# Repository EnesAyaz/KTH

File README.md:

# KTH
This repository is opened to be archival information for my coming Ph.D studies at KTH.

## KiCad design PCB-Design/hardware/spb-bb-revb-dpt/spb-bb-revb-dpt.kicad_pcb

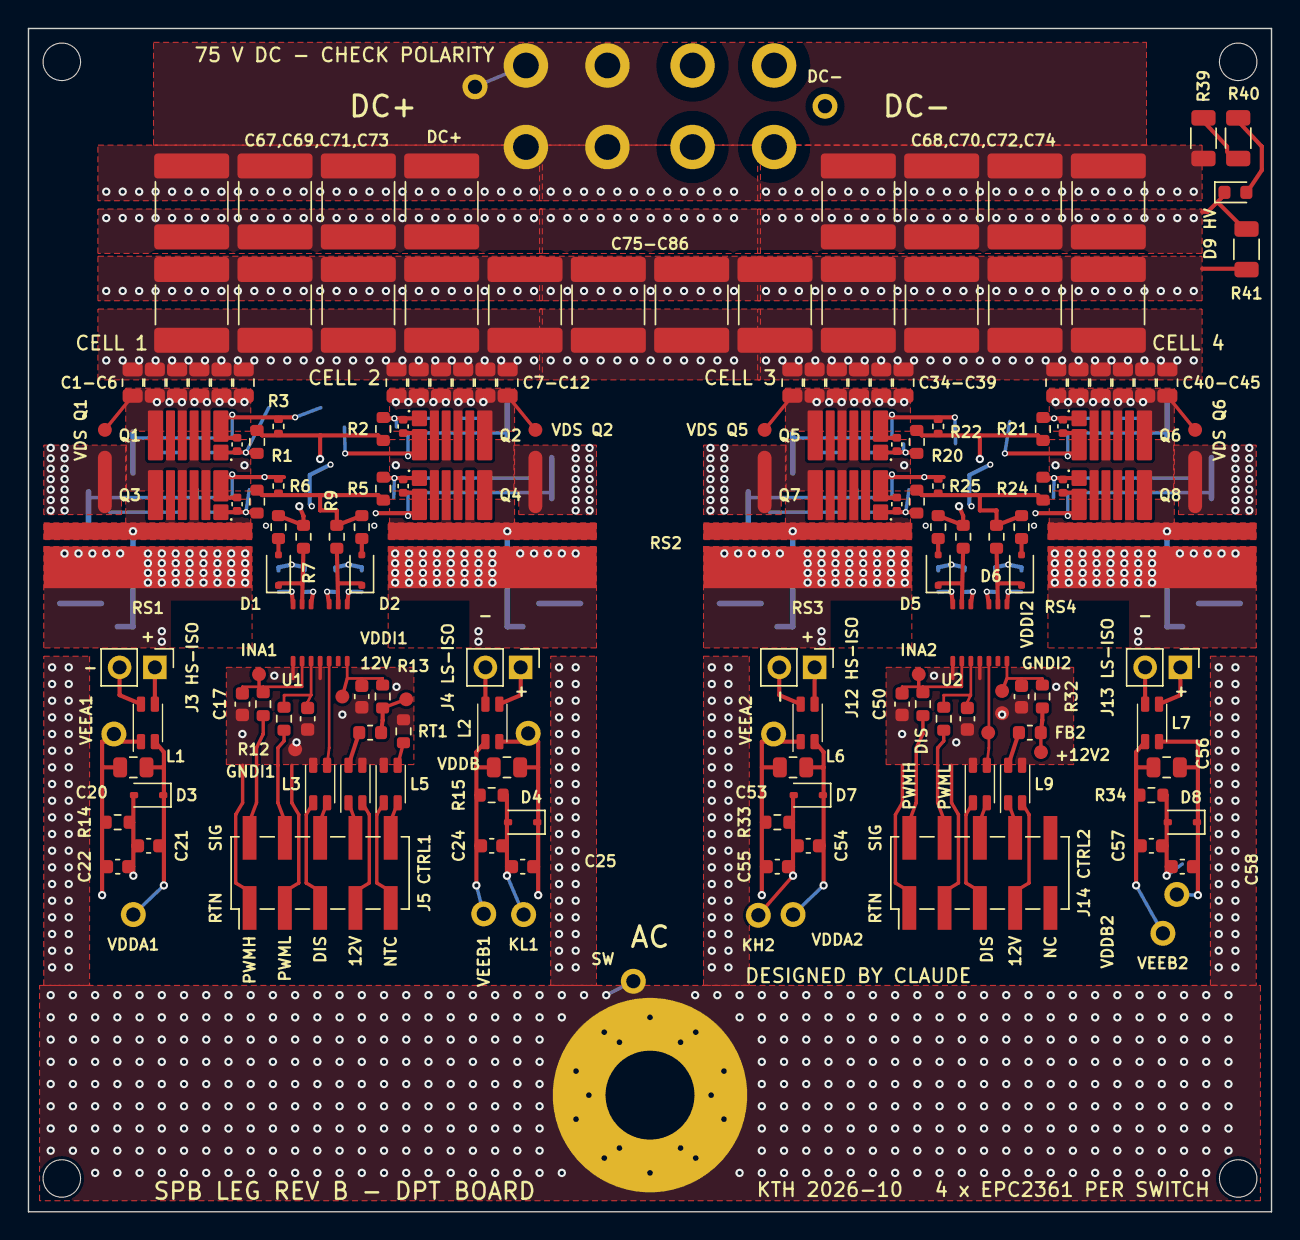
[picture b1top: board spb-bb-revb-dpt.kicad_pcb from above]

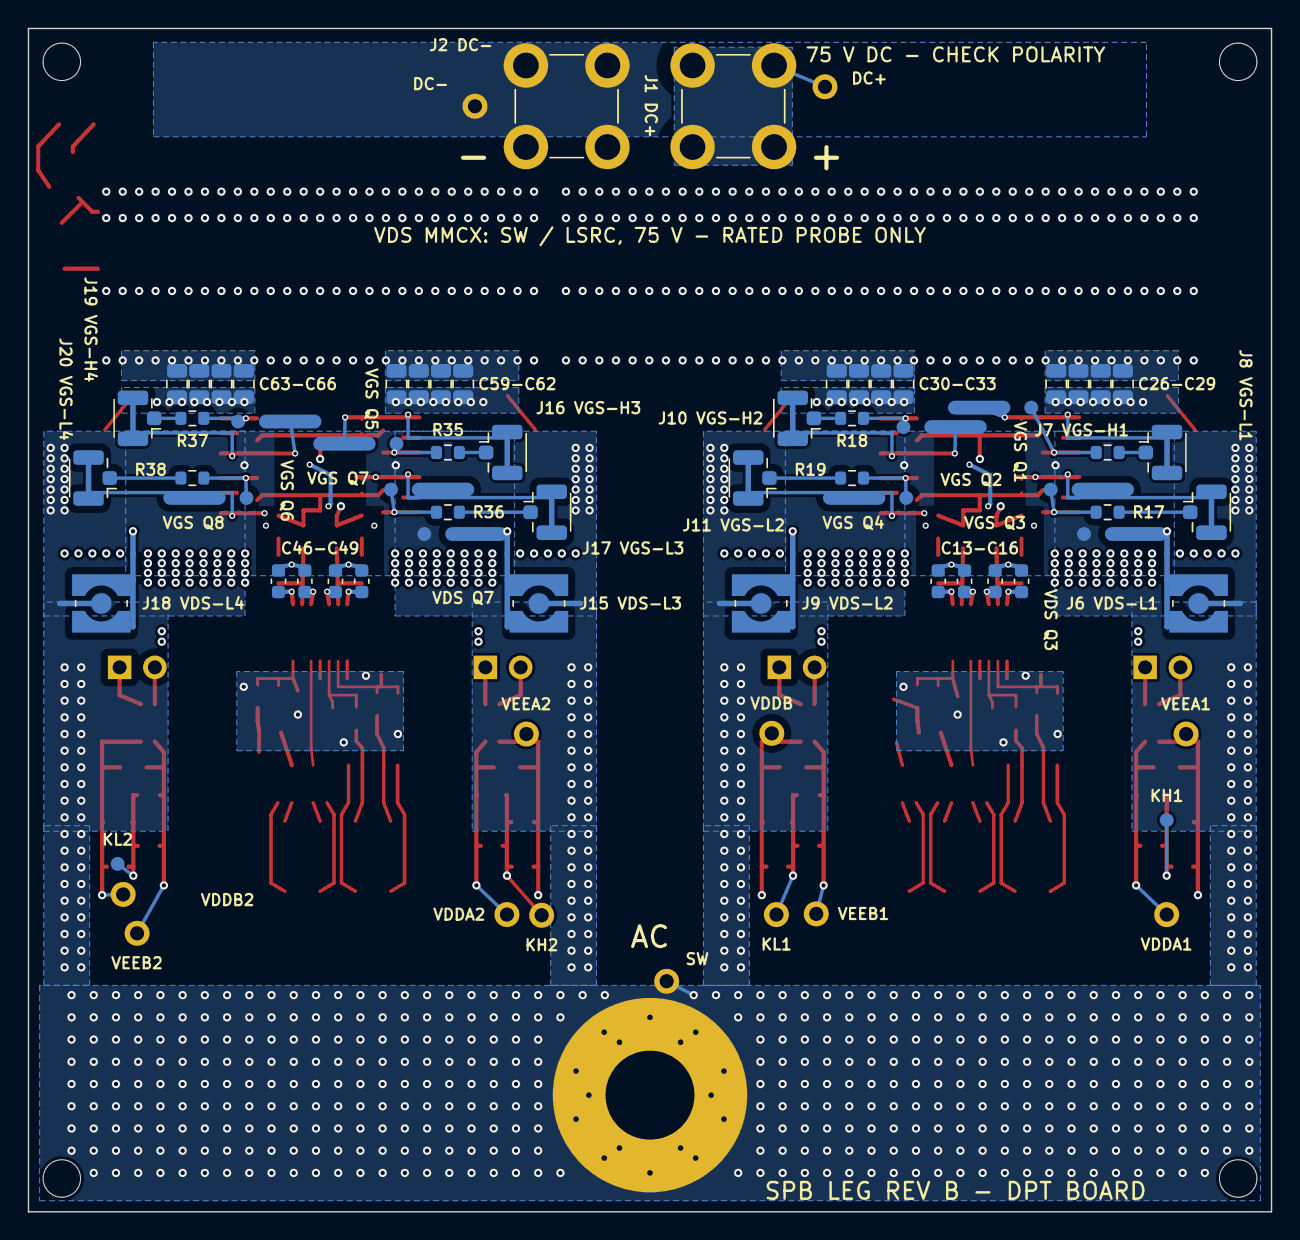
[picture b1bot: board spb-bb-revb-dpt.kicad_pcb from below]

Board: 4 copper layers, 89.5 x 85.2 mm, 233 parts (67 on the bottom side), 86 nets.

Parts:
C1, C2, C3, C4, C5, C6, C7, C8, C9, C10, C11, C12, C26, C27, C28, C29, C30, C31, C32, C33, C34, C35, C36, C37, C38, C39, C40, C41, C42, C43, C44, C45, C59, C60, C61, C62, C63, C64, C65, C66: 1uF 100V X7S; C_0805_2012Metric_TightCrtYd
C13, C14, C15, C16, C46, C47, C48, C49: 1uF 25V X7R 0603; C_0603_1608Metric
C17, C18, C50, C51: 100pF C0G 0603; C_0603_1608Metric
C19, C52: 22nF 25V X7R 0603; C_0603_1608Metric
C20, C23, C53, C56: 4.7uF 25V X7R 0805; C_0805_2012Metric
C21, C22, C24, C25, C54, C55, C57, C58: 4.7uF 16V X5R 0603; C_0603_1608Metric
C67, C68, C69, C70, C71, C72, C73, C74, C75, C76, C77, C78, C79, C80, C81, C82, C83, C84, C85, C86: 22uF 100V X7S 2220; C_2220_5750Metric_TightCrtYd
C87: DNP C_GS (Q1 gate-Kelvin, fit for tests); C_0402_1005Metric_TightCrtYd
C88: DNP C_GS (Q2 gate-Kelvin, fit for tests); C_0402_1005Metric_TightCrtYd
C89: DNP C_GS (Q3 gate-Kelvin, fit for tests); C_0402_1005Metric_TightCrtYd
C90: DNP C_GS (Q4 gate-Kelvin, fit for tests); C_0402_1005Metric_TightCrtYd
C91: DNP C_GS (Q5 gate-Kelvin, fit for tests); C_0402_1005Metric_TightCrtYd
C92: DNP C_GS (Q6 gate-Kelvin, fit for tests); C_0402_1005Metric_TightCrtYd
C93: DNP C_GS (Q7 gate-Kelvin, fit for tests); C_0402_1005Metric_TightCrtYd
C94: DNP C_GS (Q8 gate-Kelvin, fit for tests); C_0402_1005Metric_TightCrtYd
D1, D2, D5, D6: PMEG3020EJ; D_SOD-323F
D3, D4, D7, D8: BZX384-C5V1; D_SOD-323
D9: red 0603 (DC link present); LED_0603_1608Metric
FB1, FB2: BLM18PG221SN1 (220 R @ 100 MHz); L_0603_1608Metric
H1, H2, H3, H4: M2.5 insulated; MountingHole_2.7mm_M2.5
J1: DC+; Wuerth_REDCUBE-THR_WP-THRBU_74650174_THR
J2: DC-; Wuerth_REDCUBE-THR_WP-THRBU_74650174_THR
J3, J12: V_ISO,HS in: 1 +, 2 -; PinHeader_1x02_P2.54mm_Vertical
J4, J13: V_ISO,LS in: 1 +, 2 -; PinHeader_1x02_P2.54mm_Vertical
J5: CTRL1: 1 RTN 2 PWMH 3 RTN 4 PWML 5 RTN 6 DIS 7 RT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; PinHeader_2x05_P2.54mm_Vertical_SMD
J6: MMCX VDS L1; WR-MMCX_Wuerth_66012102111404_Vertical
J7: U.FL H1; U.FL_Hirose_U.FL-R-SMT-1_Vertical
J8: U.FL L1; U.FL_Hirose_U.FL-R-SMT-1_Vertical
J9: MMCX VDS L2; WR-MMCX_Wuerth_66012102111404_Vertical
J10: U.FL H2; U.FL_Hirose_U.FL-R-SMT-1_Vertical
J11: U.FL L2; U.FL_Hirose_U.FL-R-SMT-1_Vertical
J14: CTRL2: 1 RTN 2 PWMH 3 RTN 4 PWML 5 RTN 6 DIS 7 RT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; PinHeader_2x05_P2.54mm_Vertical_SMD
J15: MMCX VDS L3; WR-MMCX_Wuerth_66012102111404_Vertical
J16: U.FL H3; U.FL_Hirose_U.FL-R-SMT-1_Vertical
J17: U.FL L3; U.FL_Hirose_U.FL-R-SMT-1_Vertical
J18: MMCX VDS L4; WR-MMCX_Wuerth_66012102111404_Vertical
J19: U.FL H4; U.FL_Hirose_U.FL-R-SMT-1_Vertical
J20: U.FL L4; U.FL_Hirose_U.FL-R-SMT-1_Vertical
J21: AC; AC_BOLT_M6
L1, L2, L3, L4, L5, L6, L7, L8, L9: WE-CNSW 744232601; L_CommonMode_Wurth_WE-CNSW-1206
Q1, Q2, Q3, Q4, Q5, Q6, Q7, Q8: EPC2361
R1, R20: 0R5 1% (R_G HL); R_0603_1608Metric
R2, R21: 0R5 1% (R_G HR); R_0603_1608Metric
R3, R22: 10k 1% (HS gate pull-down); R_0402_1005Metric
R4, R23: 0R5 1% (R_G LL); R_0603_1608Metric
R5, R24: 0R5 1% (R_G LR); R_0603_1608Metric
R6, R25: 10k 1% (LS gate pull-down); R_0402_1005Metric
R7, R26: 1R5 1% (R_ON,A); R_0603_1608Metric
R8, R27: 0R (R_OFF,A); R_0603_1608Metric
R9, R28: 1R5 1% (R_ON,B); R_0603_1608Metric
R10, R29: 0R (R_OFF,B); R_0603_1608Metric
R11, R30: 47R 1% (INA); R_0603_1608Metric
R12, R31: 47R 1% (INB); R_0603_1608Metric
R13, R32: 3k 1% (RVDDI); R_0603_1608Metric
R14, R15, R33, R34: 150R 1% 0603 (bias, <= 82 mW); R_0603_1608Metric
R16, R18, R35, R37: DNP 0R (V_GS HS, fit to use the U.FL); R_0603_1608Metric
R17, R19, R36, R38: DNP 0R (V_GS LS, fit to use the U.FL); R_0603_1608Metric
R39, R40: 68k 1206 (HV LED); R_1206_3216Metric
R41: 100k 1206 (bleeder); R_1206_3216Metric
RS1, RS2, RS3, RS4: UFCS-R001; PMK_UFCS_R001_short_IN
RT1: NTC 10k B3380 0603; R_0603_1608Metric
TP1: GNDI1; TestPoint_Pad_D1.0mm
TP2: +12V1; TestPoint_Pad_D1.0mm
TP3: VDDI1; TestPoint_Pad_D1.0mm
TP4: INA1; TestPoint_Pad_D1.0mm
TP7: VDDA1; TestPoint_Keystone5000_Adafruit3825
TP8: VEEA1; TestPoint_Keystone5000_Adafruit3825
TP9: KH1; TestPoint_Pad_D1.0mm
TP11: VDDB1; TestPoint_Keystone5000_Adafruit3825
TP12: VEEB1; TestPoint_Keystone5000_Adafruit3825
TP13: KL1; TestPoint_Keystone5000_Adafruit3825
TP15: VGS Q1; TestPoint_Spring_1.0_GND1.5-6.0
TP16: VGS Q2; TestPoint_Spring_1.0_GND1.5-6.0
TP17: VGS Q3; TestPoint_Spring_1.0_GND1.5-6.0
TP18: VGS Q4; TestPoint_Spring_1.0_GND1.5-6.0
TP19: GNDI2; TestPoint_Pad_D1.0mm
TP20: +12V2; TestPoint_Pad_D1.0mm
TP21: VDDI2; TestPoint_Pad_D1.0mm
TP22: INA2; TestPoint_Pad_D1.0mm
TP24: DIS2; TestPoint_Pad_D1.0mm
TP25: VDDA2; TestPoint_Keystone5000_Adafruit3825
TP26: VEEA2; TestPoint_Keystone5000_Adafruit3825
TP27: KH2; TestPoint_Keystone5000_Adafruit3825
TP29: VDDB2; TestPoint_Keystone5000_Adafruit3825
TP30: VEEB2; TestPoint_Keystone5000_Adafruit3825
TP31: KL2; TestPoint_Pad_D1.0mm
TP33: VGS Q5; TestPoint_Spring_1.0_GND1.5-6.0
TP34: VGS Q6; TestPoint_Spring_1.0_GND1.5-6.0
TP35: VGS Q7; TestPoint_Spring_1.0_GND1.5-6.0
TP36: VGS Q8; TestPoint_Spring_1.0_GND1.5-6.0
TP37: VDS Q3; TestPoint_Spring_1.0_GND1.5-6.0
TP38: VDS Q1; TestPoint_Spring_1.0_GND1.5-6.0
TP40: VDS Q2; TestPoint_Spring_1.0_GND1.5-6.0
TP41: VDS Q7; TestPoint_Spring_1.0_GND1.5-6.0
TP42: VDS Q5; TestPoint_Spring_1.0_GND1.5-6.0
TP44: VDS Q6; TestPoint_Spring_1.0_GND1.5-6.0
TP45: DC+; TestPoint_Keystone5000_Adafruit3825
TP46: DC-; TestPoint_Keystone5000_Adafruit3825
TP47: SW; TestPoint_Keystone5000_Adafruit3825
U1, U2: 2EDF7275K; 2EDF7275K_PG-TFLGA-13-4

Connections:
12V_CM1: FB1.1, L4.2
12V_CM2: FB2.1, L9.2
+12V1: FB1.2, R13.1, TP2.1
+12V2: FB2.2, R32.1, TP20.1
C_12V1: J5.8, L4.1
C_12V2: J14.8, L9.1
C_DIS1: J5.6, L3.4
C_DIS2: J14.6, L8.4
C_NTC1: J5.10, L5.4
C_RTN_12V1: J5.7, L4.4
C_RTN_12V2: J14.7, L9.4
C_RTN_DIS1: J5.5, L3.1
C_RTN_DIS2: J14.5, L8.1
C_RTN_NTC1: J5.9, L5.1
DCN: C1.2, C2.2, C3.2, C4.2, C5.2, C6.2, C7.2, C8.2, C9.2, C10.2, C11.2, C12.2, C26.1, C27.1, C28.1, C29.1, C30.1, C31.1, C32.1, C33.1, C34.2, C35.2, C36.2, C37.2, C38.2, C39.2, C40.2, C41.2, C42.2, C43.2, C44.2, C45.2, C59.1, C60.1, C61.1, C62.1, C63.1, C64.1, C65.1, C66.1, C67.1, C68.1, C69.1, C70.1, C71.1, C72.1, C73.1, C74.1, C75.1, C76.1, C77.1, C78.1, C79.1, C80.1, C81.1, C82.1, C83.1, C84.1, C85.1, C86.1, D9.1, J2.1, R41.2, RS1.2, RS2.2, RS3.2, RS4.2, TP46.1
DCP: C1.1, C2.1, C3.1, C4.1, C5.1, C6.1, C7.1, C8.1, C9.1, C10.1, C11.1, C12.1, C26.2, C27.2, C28.2, C29.2, C30.2, C31.2, C32.2, C33.2, C34.1, C35.1, C36.1, C37.1, C38.1, C39.1, C40.1, C41.1, C42.1, C43.1, C44.1, C45.1, C59.2, C60.2, C61.2, C62.2, C63.2, C64.2, C65.2, C66.2, C67.2, C68.2, C69.2, C70.2, C71.2, C72.2, C73.2, C74.2, C75.2, C76.2, C77.2, C78.2, C79.2, C80.2, C81.2, C82.2, C83.2, C84.2, C85.2, C86.2, J1.1, Q1.3, Q1.5, Q1.7, Q2.3, Q2.5, Q2.7, Q5.3, Q5.5, Q5.7, Q6.3, Q6.5, Q6.7, R39.1, R41.1, TP38.1, TP40.1, TP42.1, TP44.1, TP45.1
DIS1: L3.3, U1.5
DIS2: L8.3, TP24.1, U2.5
GH_L1: C87.1, Q1.1, R1.1, R16.2, TP15.1
GH_L2: C91.1, Q5.1, R20.1, R35.2, TP33.1
GH_R1: C88.2, Q2.1, R2.2, R18.1, TP16.1
GH_R2: C92.2, Q6.1, R21.2, R37.1, TP34.1
GH_STAR1: R1.2, R2.1, R3.1, R7.2, R8.2
GH_STAR2: R20.2, R21.1, R22.1, R26.2, R27.2
GL_L1: C89.1, Q3.1, R4.1, R17.2, TP17.1
GL_L2: C93.1, Q7.1, R23.1, R36.2, TP35.1
GL_R1: C90.2, Q4.1, R5.2, R19.1, TP18.1
GL_R2: C94.2, Q8.1, R24.2, R38.1, TP36.1
GL_STAR1: R4.2, R5.1, R6.1, R9.2, R10.2
GL_STAR2: R23.2, R24.1, R25.1, R28.2, R29.2
GNDI1: C17.1, C18.1, C19.1, J5.1, J5.3, L3.2, L4.3, L5.2, RT1.2, TP1.1, U1.1, U1.4
GNDI2: C50.1, C51.1, C52.1, J14.1, J14.3, L8.2, L9.3, TP19.1, U2.1, U2.4
HVA: R39.2, R40.1
HVB: D9.2, R40.2
INA1: C17.2, R11.2, TP4.1, U1.2
INA2: C50.2, R30.2, TP22.1, U2.2
INB1: C18.2, R12.2, U1.3
INB2: C51.2, R31.2, U2.3
KH1: C13.1, C14.1, C21.1, C22.2, C87.2, C88.1, D3.2, J7.2, J10.2, Q1.2, Q2.2, R3.2, R14.2, TP9.1, TP15.2, TP16.2
KH2: C46.1, C47.1, C54.1, C55.2, C91.2, C92.1, D7.2, J16.2, J19.2, Q5.2, Q6.2, R22.2, R33.2, TP27.1, TP33.2, TP34.2
KL1: C15.1, C16.1, C24.2, C25.1, C89.2, C90.1, D4.2, J8.2, J11.2, Q3.2, Q4.2, R6.2, R15.2, TP13.1, TP17.2, TP18.2
KL2: C48.1, C49.1, C57.2, C58.1, C93.2, C94.1, D8.2, J17.2, J20.2, Q7.2, Q8.2, R25.2, R34.2, TP31.1, TP35.2, TP36.2
LSRC1: J6.2, Q3.4, Q3.6, RS1.1, TP37.2
LSRC2: J9.2, Q4.4, Q4.6, RS2.1
LSRC3: J15.2, Q7.4, Q7.6, RS3.1, TP41.2
LSRC4: J18.2, Q8.4, Q8.6, RS4.1
NTC: L5.3, RT1.1
OFFA1: D1.2, R8.1
OFFA2: D5.2, R27.1
OFFB1: D2.2, R10.1
OFFB2: D6.2, R29.1
OUTA1: D1.1, R7.1, U1.12
OUTA2: D5.1, R26.1, U2.12
OUTB1: D2.1, R9.1, U1.9
OUTB2: D6.1, R28.1, U2.9
PWM_H1: J5.2, R11.1
PWM_H2: J14.2, R30.1
PWM_L1: J5.4, R12.1
PWM_L2: J14.4, R31.1
SW: J6.1, J9.1, J15.1, J18.1, J21.1, Q1.4, Q1.6, Q2.4, Q2.6, Q3.3, Q3.5, Q3.7, Q4.3, Q4.5, Q4.7, Q5.4, Q5.6, Q6.4, Q6.6, Q7.3, Q7.5, Q7.7, Q8.3, Q8.5, Q8.7, TP37.1, TP38.2, TP40.2, TP41.1, TP42.2, TP44.2, TP47.1
UFL_H1: J7.1, R16.1
UFL_H2: J10.1, R18.2
UFL_H3: J16.1, R35.1
UFL_H4: J19.1, R37.2
UFL_L1: J8.1, R17.1
UFL_L2: J11.1, R19.2
UFL_L3: J17.1, R36.1
UFL_L4: J20.1, R38.2
VDDA1: C13.2, C20.2, C21.2, D3.1, L1.4, TP7.1, U1.13
VDDA2: C46.2, C53.2, C54.2, D7.1, L6.4, TP25.1, U2.13
VDDB1: C16.2, C23.2, C25.2, D4.1, L2.4, TP11.1, U1.10
VDDB2: C49.2, C56.2, C58.2, D8.1, L7.4, TP29.1, U2.10
VDDI1: C19.2, R13.2, TP3.1, U1.7
VDDI2: C52.2, R32.2, TP21.1, U2.7
VEEA1: C14.2, C20.1, C22.1, L1.1, R14.1, TP8.1, U1.11
VEEA2: C47.2, C53.1, C55.1, L6.1, R33.1, TP26.1, U2.11
VEEB1: C15.2, C23.1, C24.1, L2.1, R15.1, TP12.1, U1.8
VEEB2: C48.2, C56.1, C57.1, L7.1, R34.1, TP30.1, U2.8
VINA_N1: J3.2, L1.2
VINA_N2: J12.2, L6.2
VINA_P1: J3.1, L1.3
VINA_P2: J12.1, L6.3
VINB_N1: J4.2, L2.2
VINB_N2: J13.2, L7.2
VINB_P1: J4.1, L2.3
VINB_P2: J13.1, L7.3

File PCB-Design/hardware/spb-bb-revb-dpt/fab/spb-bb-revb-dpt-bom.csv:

"# 4 layers, 1.6 mm FR4, 2 oz (70 um) on all layers, L1-L2 and L3-L4 prepreg 0.1 mm, ENIG; filled + capped via-in-pad (list in gerber/*-fab-notes.txt: shunt SHLD, bypass-capacitor and test pads); double-pulse board (UFCS shunts, no heatsink); IPC class 2; solder mask over all copper and ALL vias tented (the 1200 V control/power barrier relies on it)"
Qty,References,Value,Footprint,Manufacturer part / note,Fit
1,J1,DC+,Wuerth_REDCUBE-THR_WP-THRBU_74650174_THR,"Wuerth 74650174 (REDCUBE THR, M4)",fit
1,J2,DC-,Wuerth_REDCUBE-THR_WP-THRBU_74650174_THR,"Wuerth 74650174 (REDCUBE THR, M4)",fit
8,Q1 Q2 Q3 Q4 Q5 Q6 Q7 Q8,EPC2361,EPC2361,EPC2361,fit
40,C1 C2 C3 C4 C5 C6 C7 C8 C9 C10 C11 C12 C26 C27 C28 C29 C30 C31 C32 C33 C34 C35 C36 C37 C38 C39 C40 C41 C42 C43 C44 C45 C59 C60 C61 C62 C63 C64 C65 C66,1uF 100V X7S,C_0805_2012Metric_TightCrtYd,TDK C2012X7S2A105K125AB,fit
2,R1 R20,0R5 1% (R_G HL),R_0603_1608Metric,0.5R 0603 1% (Panasonic ERJ-3BQFR50V),fit
2,R2 R21,0R5 1% (R_G HR),R_0603_1608Metric,0.5R 0603 1% (Panasonic ERJ-3BQFR50V),fit
2,R3 R22,10k 1% (HS gate pull-down),R_0402_1005Metric,10k 0402 1%,fit
2,R4 R23,0R5 1% (R_G LL),R_0603_1608Metric,0.5R 0603 1% (Panasonic ERJ-3BQFR50V),fit
2,R5 R24,0R5 1% (R_G LR),R_0603_1608Metric,0.5R 0603 1% (Panasonic ERJ-3BQFR50V),fit
2,R6 R25,10k 1% (LS gate pull-down),R_0402_1005Metric,10k 0402 1%,fit
2,U1 U2,2EDF7275K,2EDF7275K_PG-TFLGA-13-4,Infineon 2EDF7275KXUMA1,fit
2,R7 R26,"1R5 1% (R_ON,A)",R_0603_1608Metric,1.5R 0603 1% (Yageo RC0603FR-071R5L),fit
2,R8 R27,"0R (R_OFF,A)",R_0603_1608Metric,0R 0603 jumper (set R_OFF here),fit
4,D1 D2 D5 D6,PMEG3020EJ,D_SOD-323F,"Nexperia PMEG3020EJ (30 V, 2 A, SOD323F)",fit
2,R9 R28,"1R5 1% (R_ON,B)",R_0603_1608Metric,1.5R 0603 1% (Yageo RC0603FR-071R5L),fit
2,R10 R29,"0R (R_OFF,B)",R_0603_1608Metric,0R 0603 jumper (set R_OFF here),fit
8,C13 C14 C15 C16 C46 C47 C48 C49,1uF 25V X7R 0603,C_0603_1608Metric,TDK C1608X7R1E105K080AB,fit
4,C17 C18 C50 C51,100pF C0G 0603,C_0603_1608Metric,Murata GRM1885C1H101JA01,fit
2,R11 R30,47R 1% (INA),R_0603_1608Metric,47R 0603 1%,fit
2,R12 R31,47R 1% (INB),R_0603_1608Metric,47R 0603 1%,fit
2,C19 C52,22nF 25V X7R 0603,C_0603_1608Metric,Murata GRM188R71E223KA01,fit
2,R13 R32,3k 1% (RVDDI),R_0603_1608Metric,3.0k 0603 1%,fit
4,RS1 RS2 RS3 RS4,UFCS-R001,PMK_UFCS_R001_short_IN,"PMK UFCS-R001 (1 mOhm, 50 A cont.)","NOT by the assembler: hand-soldered in the lab at the blade (short IN land), SMA cable to the scope"
2,J3 J12,"V_ISO,HS in: 1 +, 2 -",PinHeader_1x02_P2.54mm_Vertical,2.54 mm header 1x2,fit
9,L1 L2 L3 L4 L5 L6 L7 L8 L9,WE-CNSW 744232601,L_CommonMode_Wurth_WE-CNSW-1206,"Wurth 744232601 (600 Ohm @ 100 MHz, 260 mA)",fit
4,C20 C23 C53 C56,4.7uF 25V X7R 0805,C_0805_2012Metric,Murata GRM21BR71E475KA73,fit
4,D3 D4 D7 D8,BZX384-C5V1,D_SOD-323,"Nexperia BZX384-C5V1 (5.1 V, 300 mW)",fit
4,R14 R15 R33 R34,"150R 1% 0603 (bias, <= 82 mW)",R_0603_1608Metric,150R 0603 1% 0.1 W,fit
8,C21 C22 C24 C25 C54 C55 C57 C58,4.7uF 16V X5R 0603,C_0603_1608Metric,Murata GRM188R61C475KAAJ,fit
2,J4 J13,"V_ISO,LS in: 1 +, 2 -",PinHeader_1x02_P2.54mm_Vertical,2.54 mm header 1x2,fit
1,J5,CTRL1: 1 RTN 2 PWMH 3 RTN 4 PWML 5 RTN 6 DIS 7 RTN 8 12V 9 RTN 10 NTC,PinHeader_2x05_P2.54mm_Vertical_SMD,"Samtec TSM-105-01-T-DV (2 x 5, 2.54 mm, SMT)",fit
2,FB1 FB2,BLM18PG221SN1 (220 R @ 100 MHz),L_0603_1608Metric,"Murata BLM18PG221SN1D (ferrite bead, 1.4 A)",fit
1,RT1,NTC 10k B3380 0603,R_0603_1608Metric,Murata NCP18XH103F03RB,fit
1,J6,MMCX VDS L1,WR-MMCX_Wuerth_66012102111404_Vertical,"Wurth 66012102111404 (WR-MMCX PCB SMT jack, vertical, 170 V rms)",fit
1,J7,U.FL H1,U.FL_Hirose_U.FL-R-SMT-1_Vertical,Hirose U.FL-R-SMT-1(10),fit
4,R16 R18 R35 R37,"DNP 0R (V_GS HS, fit to use the U.FL)",R_0603_1608Metric,0R 0603 - not fitted by default,DNP
1,J8,U.FL L1,U.FL_Hirose_U.FL-R-SMT-1_Vertical,Hirose U.FL-R-SMT-1(10),fit
4,R17 R19 R36 R38,"DNP 0R (V_GS LS, fit to use the U.FL)",R_0603_1608Metric,0R 0603 - not fitted by default,DNP
1,J9,MMCX VDS L2,WR-MMCX_Wuerth_66012102111404_Vertical,"Wurth 66012102111404 (WR-MMCX PCB SMT jack, vertical, 170 V rms)",fit
1,J10,U.FL H2,U.FL_Hirose_U.FL-R-SMT-1_Vertical,Hirose U.FL-R-SMT-1(10),fit
1,J11,U.FL L2,U.FL_Hirose_U.FL-R-SMT-1_Vertical,Hirose U.FL-R-SMT-1(10),fit
1,J14,CTRL2: 1 RTN 2 PWMH 3 RTN 4 PWML 5 RTN 6 DIS 7 RTN 8 12V 9 NC 10 NC,PinHeader_2x05_P2.54mm_Vertical_SMD,"Samtec TSM-105-01-T-DV (2 x 5, 2.54 mm, SMT)",fit
1,J15,MMCX VDS L3,WR-MMCX_Wuerth_66012102111404_Vertical,"Wurth 66012102111404 (WR-MMCX PCB SMT jack, vertical, 170 V rms)",fit
1,J16,U.FL H3,U.FL_Hirose_U.FL-R-SMT-1_Vertical,Hirose U.FL-R-SMT-1(10),fit
1,J17,U.FL L3,U.FL_Hirose_U.FL-R-SMT-1_Vertical,Hirose U.FL-R-SMT-1(10),fit
1,J18,MMCX VDS L4,WR-MMCX_Wuerth_66012102111404_Vertical,"Wurth 66012102111404 (WR-MMCX PCB SMT jack, vertical, 170 V rms)",fit
1,J19,U.FL H4,U.FL_Hirose_U.FL-R-SMT-1_Vertical,Hirose U.FL-R-SMT-1(10),fit
1,J20,U.FL L4,U.FL_Hirose_U.FL-R-SMT-1_Vertical,Hirose U.FL-R-SMT-1(10),fit
20,C67 C68 C69 C70 C71 C72 C73 C74 C75 C76 C77 C78 C79 C80 C81 C82 C83 C84 C85 C86,22uF 100V X7S 2220,C_2220_5750Metric_TightCrtYd,TDK C5750X7S2A226M280KB,fit
2,R39 R40,68k 1206 (HV LED),R_1206_3216Metric,68k 1206 1% 200 V,fit
1,D9,red 0603 (DC link present),LED_0603_1608Metric,Wurth 150060RS75000,fit
1,R41,100k 1206 (bleeder),R_1206_3216Metric,100k 1206 1% 200 V,fit
1,C87,"DNP C_GS (Q1 gate-Kelvin, fit for tests)",C_0402_1005Metric_TightCrtYd,"0402 C0G/X7R, value per test - not fitted by default",DNP
1,C88,"DNP C_GS (Q2 gate-Kelvin, fit for tests)",C_0402_1005Metric_TightCrtYd,"0402 C0G/X7R, value per test - not fitted by default",DNP
1,C89,"DNP C_GS (Q3 gate-Kelvin, fit for tests)",C_0402_1005Metric_TightCrtYd,"0402 C0G/X7R, value per test - not fitted by default",DNP
1,C90,"DNP C_GS (Q4 gate-Kelvin, fit for tests)",C_0402_1005Metric_TightCrtYd,"0402 C0G/X7R, value per test - not fitted by default",DNP
1,C91,"DNP C_GS (Q5 gate-Kelvin, fit for tests)",C_0402_1005Metric_TightCrtYd,"0402 C0G/X7R, value per test - not fitted by default",DNP
1,C92,"DNP C_GS (Q6 gate-Kelvin, fit for tests)",C_0402_1005Metric_TightCrtYd,"0402 C0G/X7R, value per test - not fitted by default",DNP
1,C93,"DNP C_GS (Q7 gate-Kelvin, fit for tests)",C_0402_1005Metric_TightCrtYd,"0402 C0G/X7R, value per test - not fitted by default",DNP
1,C94,"DNP C_GS (Q8 gate-Kelvin, fit for tests)",C_0402_1005Metric_TightCrtYd,"0402 C0G/X7R, value per test - not fitted by default",DNP

Mechanical (not placed by the assembler)
2,J1-J2,M4 x 8 screw + washer into REDCUBE (to the DC source / busbar),-,"steel, A2"
1,J21,"M6 x 16 bolt + nut + 2 washers, AC bolt pad",-,"steel, A2"
1,J21,"AC bar 12 x 5 mm Cu, M6 hole, length to the load inductor",-,"Cu-ETP, tin plated"
4,H1-H4,M2.5 standoff + screw (board mounting),-,nylon / insulated
2,"J5, J14",Control cable: 2 x 5 IDC socket + ribbon (each signal next to its own return),-,"2.54 mm IDC, e.g. Wurth 61201021621"
4,J6 J9 J15 J18,"V_DS lab cable: MMCX plug to BNC male, RG316, about 15 cm (to a differential probe, never straight to the scope)",-,e.g. Pasternack PE3C1904; confirm MMCX plug and BNC male
1,lab,BNC to 4 mm adapter at the differential probe input (type follows the probe input),-,4 mm sockets on probe: Farnell CT3889; 4 mm plugs on probe: PMK 4MM-BNC-F
1,lab,"High-voltage differential probe, above 100 V differential, BNC output",-,not chosen yet; see reports/pcb-rules/DPT_measurement_setup.md
13,TP7 TP8 TP11 TP12 TP13 TP25 TP26 TP27 TP29 TP30 TP45 TP46 TP47,"Loop test point, red, 0.1 in bushing, 1.02 mm (0.040 in) hole (inserted in the lab, not by the assembler; see fab/testpoints.csv)",TestPoint_Keystone5000_Adafruit3825,"Adafruit 3825 (PiShop 1752), equivalent Keystone 5000 (red) / 5001 (black)"
